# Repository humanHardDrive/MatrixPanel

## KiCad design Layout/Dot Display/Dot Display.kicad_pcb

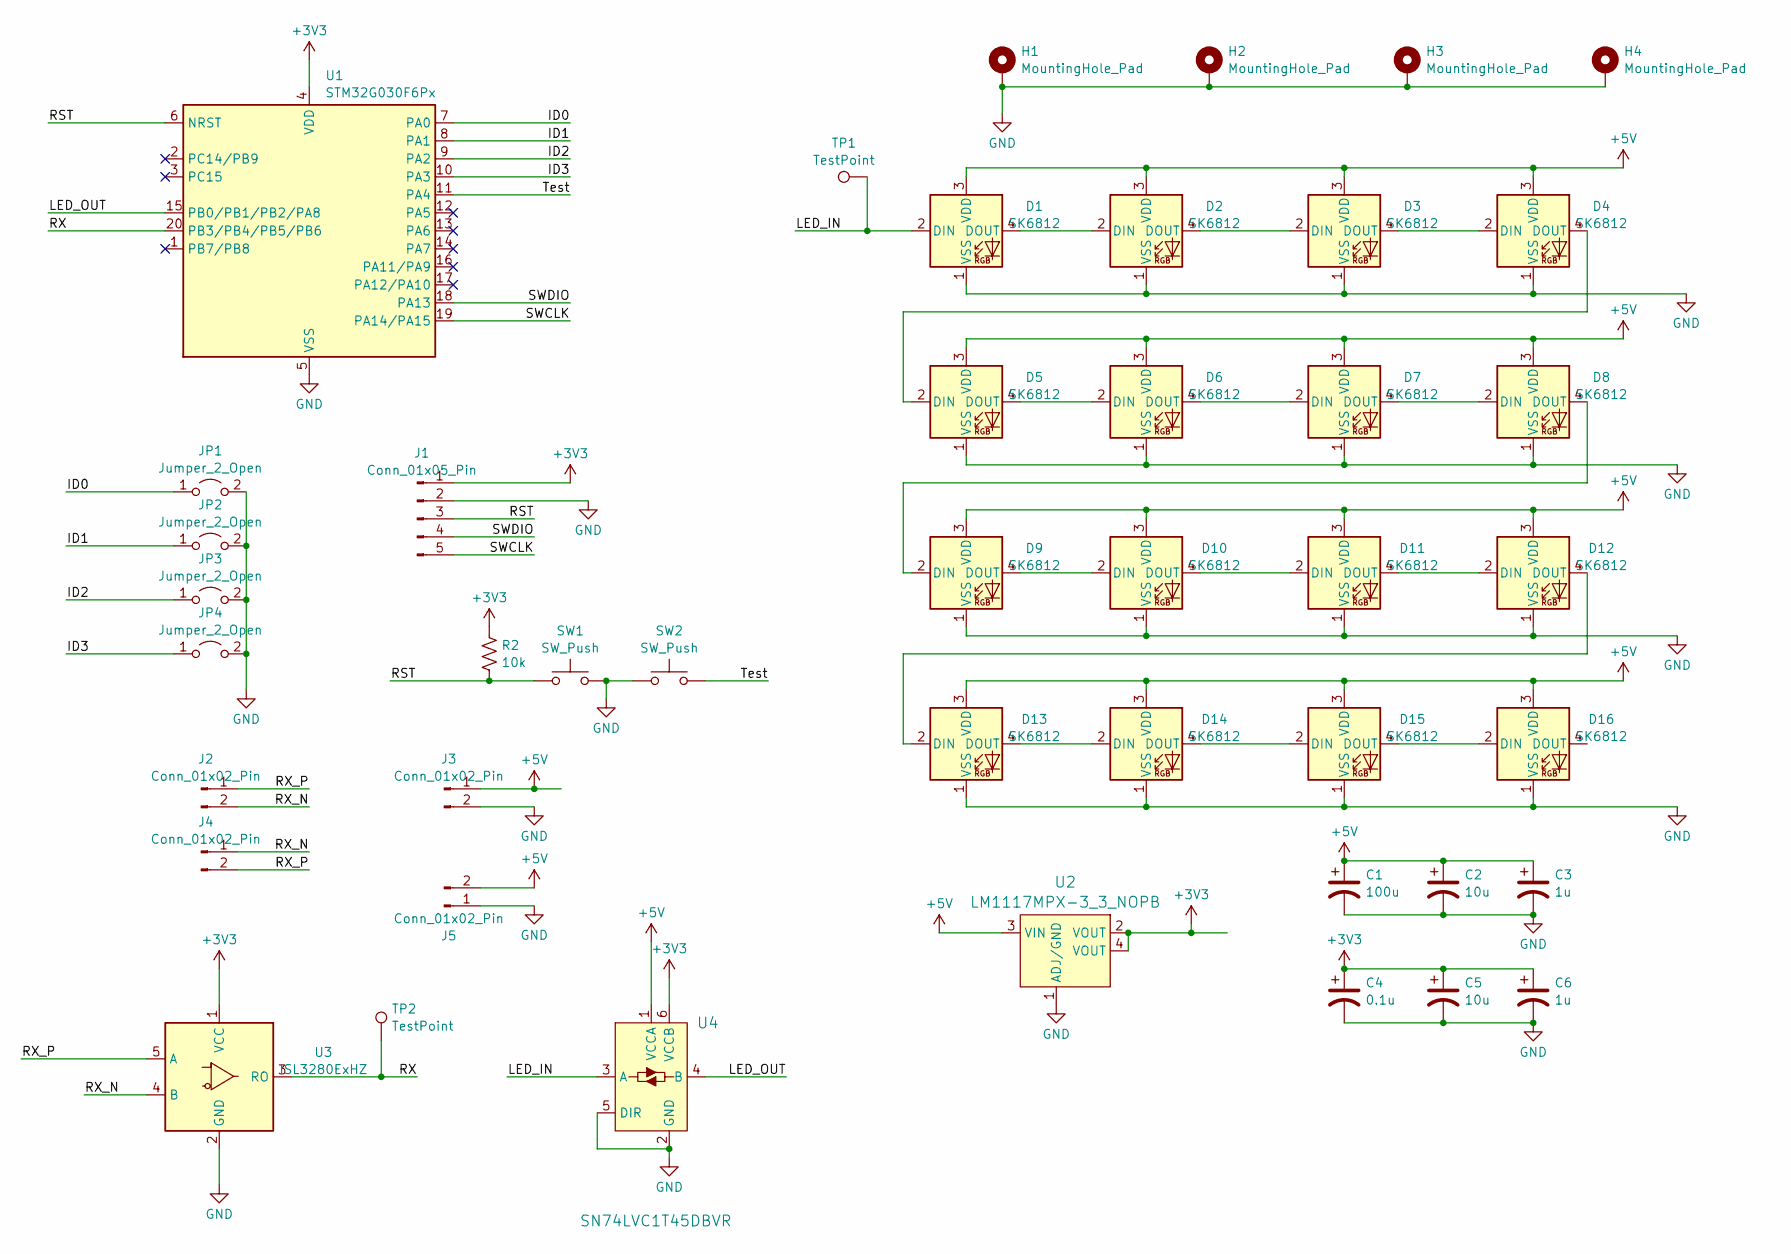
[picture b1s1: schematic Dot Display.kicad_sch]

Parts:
C1: 100u; C_0805_2012Metric
C2, C5: 10u; C_0805_2012Metric
C3, C6: 1u; C_0805_2012Metric
C4: 0.1u; C_0805_2012Metric
D1, D2, D3, D4, D5, D6, D7, D8, D9, D10, D11, D12, D13, D14, D15, D16: SK6812; LED_SK6812_PLCC4_5.0x5.0mm_P3.2mm
H1, H2, H3, H4: MountingHole_Pad; MountingHole_3.2mm_M3_DIN965_Pad
J1: Conn_01x05_Pin; Harwin_M20-89005xx_1x05_P2.54mm_Horizontal
J2, J3, J4, J5: Conn_01x02_Pin; 23839382
JP1, JP2, JP3, JP4: Jumper_2_Open; SolderJumper-2_P1.3mm_Open_RoundedPad1.0x1.5mm
R2: 10k; R_0805_2012Metric
SW1, SW2: SW_Push; SW_SPST_TL3342
TP1, TP2: TestPoint; TestPoint_Pad_D2.5mm
U1: STM32G030F6Px; TSSOP-20_4.4x6.5mm_P0.65mm
U2: LM1117MPX-3_3_NOPB; SOT-223; MPN LM1117MPX-3.3/NOPB; Digi-Key_PN LM1117MPX-3.3/NOPBCT-ND
U3: ISL3280ExHZ; SOT-23-5
U4: SN74LVC1T45DBVR; SOT-23-6; MPN SN74LVC1T45DBVR; Digi-Key_PN 296-16843-1-ND

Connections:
+3V3: C4.1, C5.1, C6.1, J1.1, R2.1, U1.4 (VDD), U2.2 (VOUT), U2.4 (VOUT), U3.1 (VCC), U4.6 (VCCB)
+5V: C1.1, C2.1, C3.1, D1.3 (VDD), D2.3 (VDD), D3.3 (VDD), D4.3 (VDD), D5.3 (VDD), D6.3 (VDD), D7.3 (VDD), D8.3 (VDD), D9.3 (VDD), D10.3 (VDD), D11.3 (VDD), D12.3 (VDD), D13.3 (VDD), D14.3 (VDD), D15.3 (VDD), D16.3 (VDD), J3.1, J5.2, U2.3 (VIN), U4.1 (VCCA)
/ID0: JP1.1 (A), U1.7 (PA0)
/ID1: JP2.1 (A), U1.8 (PA1)
/ID2: JP3.1 (A), U1.9 (PA2)
/ID3: JP4.1 (A), U1.10 (PA3)
/LED_IN: D1.2 (DIN), TP1.1, U4.3 (A)
/LED_OUT: U1.15 (PB0/PB1/PB2/PA8), U4.4 (B)
/RST: J1.3, R2.2, SW1.1, U1.6 (NRST)
/RX: TP2.1, U1.20 (PB3/PB4/PB5/PB6), U3.3 (RO)
/RX_N: J2.2, J4.1, U3.4 (B)
/RX_P: J2.1, J4.2, U3.5 (A)
/SWCLK: J1.5, U1.19 (PA14/PA15)
/SWDIO: J1.4, U1.18 (PA13)
/Test: SW2.2, U1.11 (PA4)
GND: C1.2, C2.2, C3.2, C4.2, C5.2, C6.2, D1.1 (VSS), D2.1 (VSS), D3.1 (VSS), D4.1 (VSS), D5.1 (VSS), D6.1 (VSS), D7.1 (VSS), D8.1 (VSS), D9.1 (VSS), D10.1 (VSS), D11.1 (VSS), D12.1 (VSS), D13.1 (VSS), D14.1 (VSS), D15.1 (VSS), D16.1 (VSS), H1.1, H2.1, H3.1, H4.1, J1.2, J3.2, J5.1, JP1.2 (B), JP2.2 (B), JP3.2 (B), JP4.2 (B), SW1.2, SW2.1, U1.5 (VSS), U2.1 (ADJ/GND), U3.2 (GND), U4.2 (GND), U4.5 (DIR)
unnamed: D1.4 (DOUT), D2.2 (DIN)
unnamed: D2.4 (DOUT), D3.2 (DIN)
unnamed: D3.4 (DOUT), D4.2 (DIN)
unnamed: D4.4 (DOUT), D5.2 (DIN)
unnamed: D5.4 (DOUT), D6.2 (DIN)
unnamed: D6.4 (DOUT), D7.2 (DIN)
unnamed: D7.4 (DOUT), D8.2 (DIN)
unnamed: D8.4 (DOUT), D9.2 (DIN)
unnamed: D9.4 (DOUT), D10.2 (DIN)
unnamed: D10.4 (DOUT), D11.2 (DIN)
unnamed: D11.4 (DOUT), D12.2 (DIN)
unnamed: D12.4 (DOUT), D13.2 (DIN)
unnamed: D13.4 (DOUT), D14.2 (DIN)
unnamed: D14.4 (DOUT), D15.2 (DIN)
unnamed: D15.4 (DOUT), D16.2 (DIN)

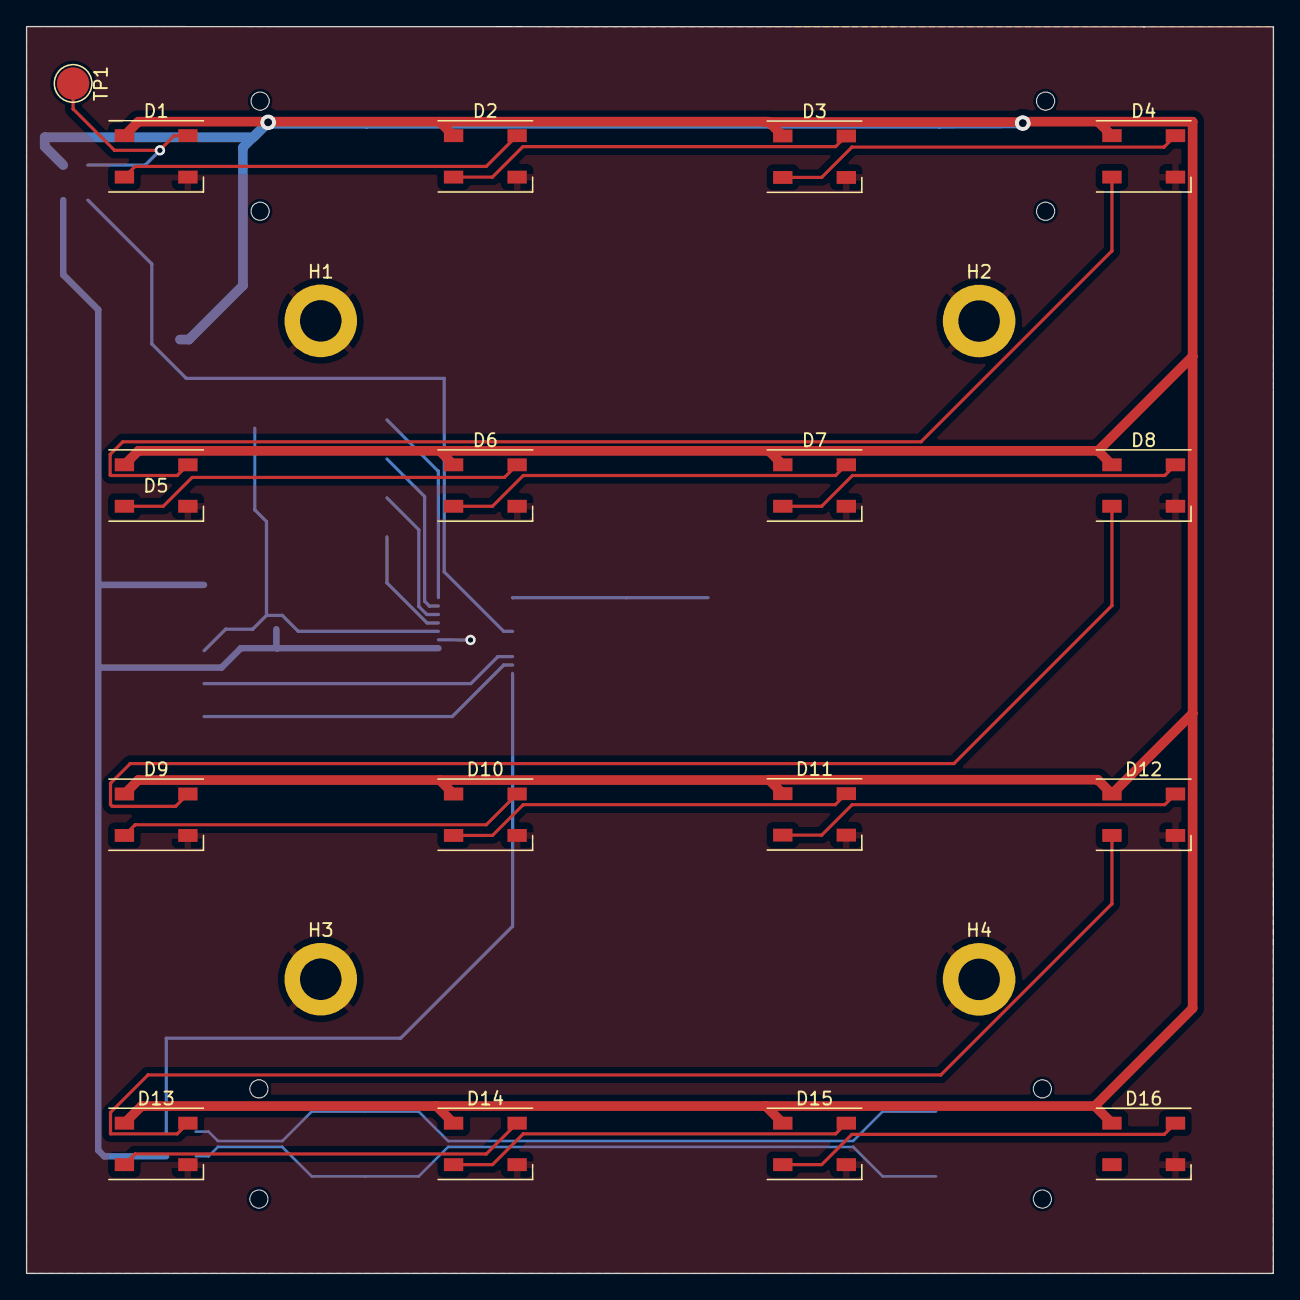
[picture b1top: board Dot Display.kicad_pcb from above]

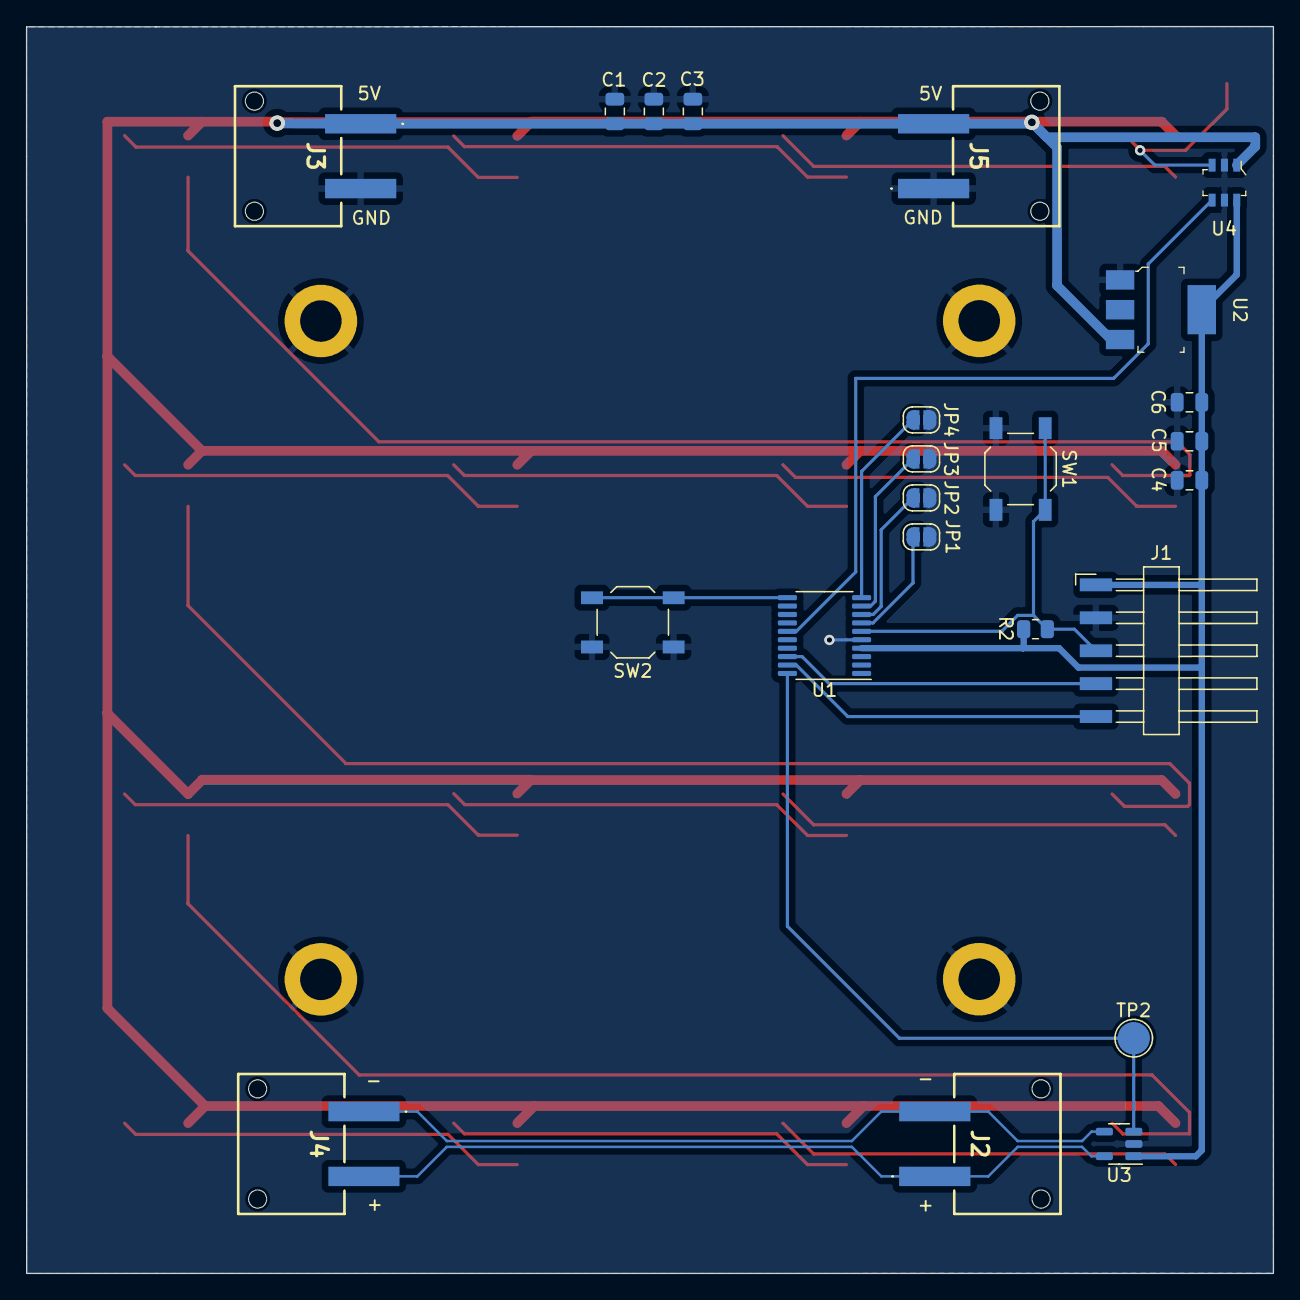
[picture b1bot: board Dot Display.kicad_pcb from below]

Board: 2 copper layers, 96.2 x 96.2 mm, 44 parts (23 on the bottom side), 31 nets.

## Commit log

2024-03-02 Initial checkin
2024-03-03 Setup DMA to control light
